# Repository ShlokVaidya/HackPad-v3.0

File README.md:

# HackPad v3.0

### Schematic

### PCB

### 3D

### 3D case

### Final Product

### bom.csv

## Features

- Uses Seeed XIAO RP2040, a small form factor board based on the Raspberry Pi RP2040 microcontroller.
- Supports MicroPython and CircuitPython.
- Kailh hot-swappable sockets compatible with 3-pin and 5-pin MX switches.
- Rotary quadrature encoder with push button.
- SK6812 reverse-mounted addressable RGB LEDs to backlight each key.
- Power and communication through a USB-C type port.
- Compatible with KMK keyboard firmware.
- Compatible with Windows, macOS, and Linux operating systems.
- Dimensions: 61mm x 81mm x 31mm (without case), 66mm x 86mm x 35mm (with 3D-printed case).

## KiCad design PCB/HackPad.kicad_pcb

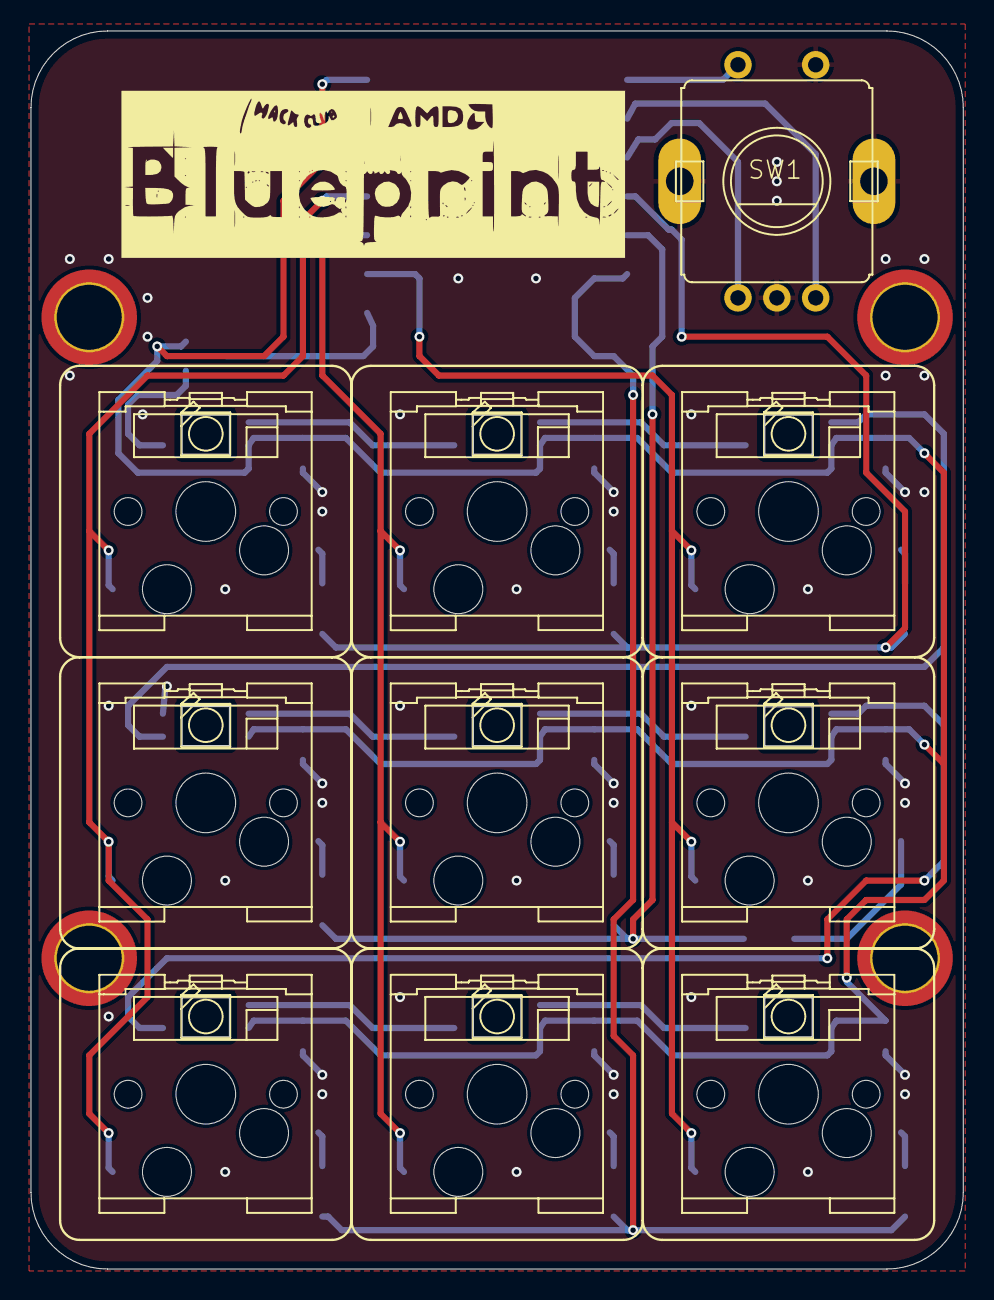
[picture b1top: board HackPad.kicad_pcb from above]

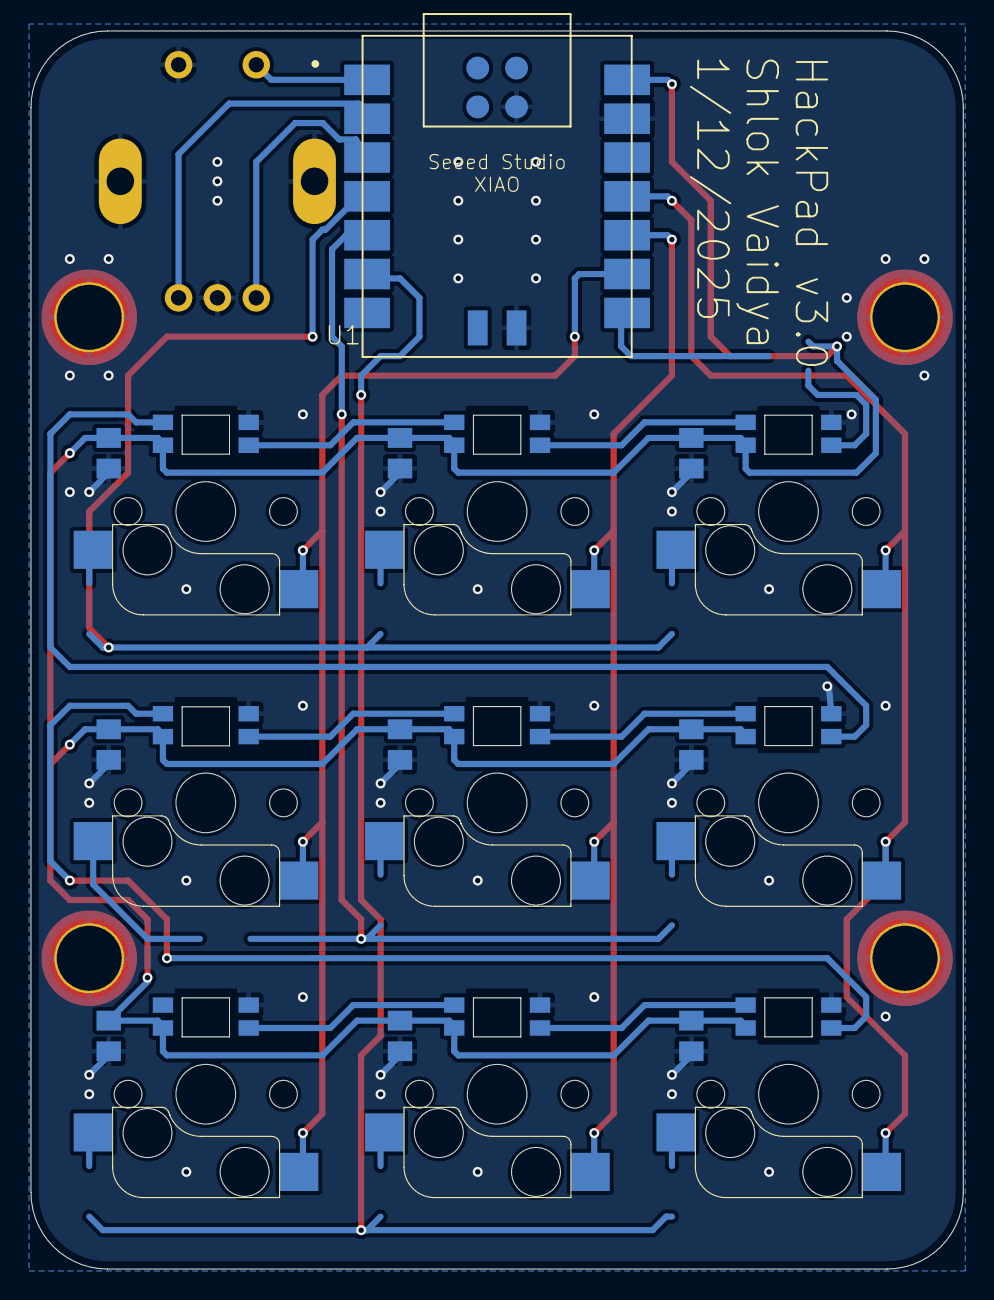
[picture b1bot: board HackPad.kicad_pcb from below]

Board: 2 copper layers, 61.0 x 81.0 mm, 33 parts (10 on the bottom side), 16 nets.

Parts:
C1, C2, C3, C4, C5, C6, C7, C8, C9: 0.1uF; C0805K_334
LED1, LED2, LED3, LED4, LED5, LED6, LED7, LED8, LED9: MICROBUILDER_WS2812B_SK6812E; MICROBUILDER_NEO3535_REVERSE
S1, S2, S3, S4, S5, S6, S7, S8, S9: SOCKET; ADAFRUIT_ELECTROMECH_KAILH_SOCKET
SW1: PEC11; ADAFRUIT_ELECTROMECH_PEC11+SWITCH
TP1, TP2, TP3, TP4: SEWTAP_SMTNUTM3; SMT_NUT_3MM
U1: SEEED-STUDIO-XIAO-SERIES_XIAO-RP2040; SEEED-STUDIO-XIAO-SERIES_XIAO-SAMD21_RP2040-MODULE14P-2.54-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

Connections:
+5V: C1.1, C2.1, C3.1, C4.1, C5.1, C6.1, C7.1, C8.1, C9.1, LED1.1-VDD, LED2.1-VDD, LED3.1-VDD, LED4.1-VDD, LED5.1-VDD, LED6.1-VDD, LED7.1-VDD, LED8.1-VDD, LED9.1-VDD, U1.14
BTN: SW1.P$1, U1.1
COL1: S1.1, S4.1, S7.1, U1.11
COL2: S2.1, S5.1, S8.1, U1.10
COL3: S3.1, S6.1, S9.1, U1.9
GND: C1.2, C2.2, C3.2, C4.2, C5.2, C6.2, C7.2, C8.2, C9.2, LED1.3-GND, LED2.3-GND, LED3.3-GND, LED4.3-GND, LED5.3-GND, LED6.3-GND, LED7.3-GND, LED8.3-GND, LED9.3-GND, SW1.P$2, SW1.P$C, SW1.P$GND1, SW1.P$GND2, TP1.P$1, TP2.P$1, TP3.P$1, TP4.P$1, U1.13, U1.18, U1.20
unnamed: LED8.2-DOUT, LED9.4-DIN
unnamed: LED7.2-DOUT, LED8.4-DIN
unnamed: LED5.2-DOUT, LED6.4-DIN
unnamed: LED6.2-DOUT, LED7.4-DIN
unnamed: LED4.2-DOUT, LED5.4-DIN
unnamed: LED3.2-DOUT, LED4.4-DIN
unnamed: LED1.2-DOUT, LED2.4-DIN
unnamed: LED2.2-DOUT, LED3.4-DIN
ROTA: SW1.P$A, U1.3
ROTB: SW1.P$B, U1.2

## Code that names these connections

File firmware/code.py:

import board
from kmk.kmk_keyboard import KMKKeyboard
from kmk.keys import KC
from kmk.scanners import DiodeOrientation
from kmk.extensions.RGB import RGB, AnimationModes
from kmk.extensions.media_keys import MediaKeys
from kmk.modules.encoder import EncoderHandler

# Pinout
COL1 = board.D10
COL2 = board.D9
COL3 = board.D8
ROW1 = board.D3
ROW2 = board.D4
ROW3 = board.D5
PUSHBUTTON = board.D0
ROTA = board.D2
ROTB = board.D1
NEOPIXEL = board.D7

keyboard = KMKKeyboard()

# Basic matrix settings
keyboard.col_pins = (COL1, COL2, COL3)
keyboard.row_pins = (ROW1, ROW2, ROW3)
keyboard.diode_orientation = DiodeOrientation.COL2ROW

# RGB LEDs settings
rgb_ext = RGB( 
    pixel_pin = NEOPIXEL,
    num_pixels = 9,
    hue_default = 100,
    sat_default = 255,
    val_default = 15,
    val_limit = 25,
    animation_speed = 1,
    animation_mode=AnimationModes.RAINBOW,
    refresh_rate = 30,
)
keyboard.extensions.append(rgb_ext)
keyboard.extensions.append(MediaKeys())

# Encoder settings
encoder_handler = EncoderHandler()
keyboard.modules.append(encoder_handler)
encoder_handler.pins = ((ROTA, ROTB, PUSHBUTTON, False),)
encoder_handler.map = (((KC.VOLD, KC.VOLU, KC.MUTE),),)

# Keymap
keyboard.keymap = [
    [KC.LCTRL(KC.LSHIFT(KC.TAB)), KC.LCTRL(KC.M), KC.LCTRL(KC.TAB),
     KC.MEDIA_PREV_TRACK, KC.MEDIA_PLAY_PAUSE, KC.MEDIA_NEXT_TRACK,
     KC.LCTRL(KC.C), KC.LCTRL(KC.V), KC.LGUI(KC.SPACE),
    ]
]

if __name__ == '__main__':
    keyboard.go()

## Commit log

2025-12-01 HackPad v3.0
2025-12-01 V3.1
2025-12-02 Added bom.csv
2025-12-02 Add SVG image for bom in README
